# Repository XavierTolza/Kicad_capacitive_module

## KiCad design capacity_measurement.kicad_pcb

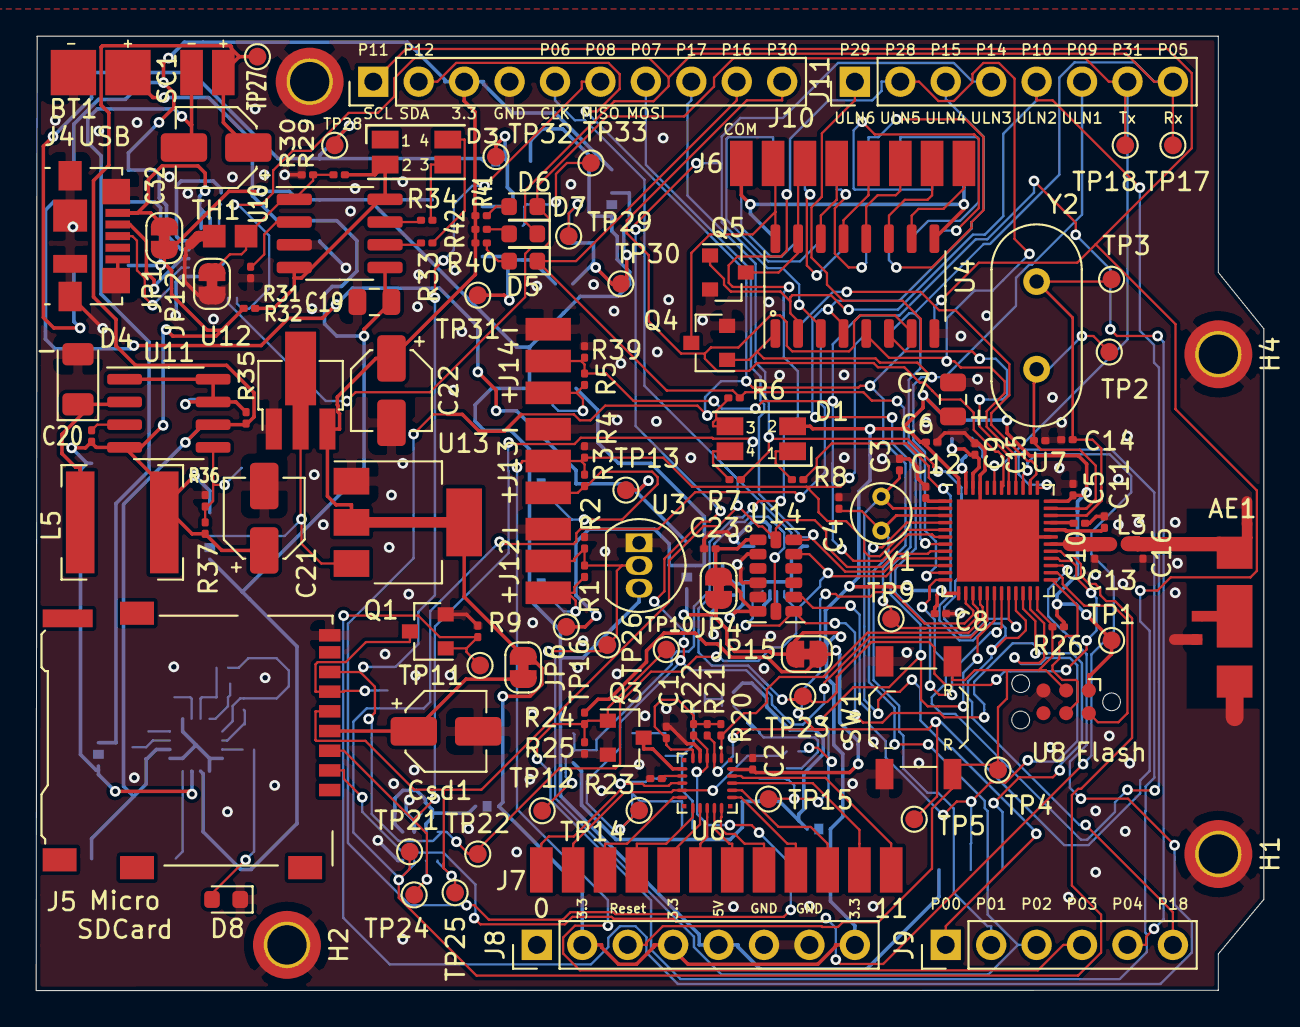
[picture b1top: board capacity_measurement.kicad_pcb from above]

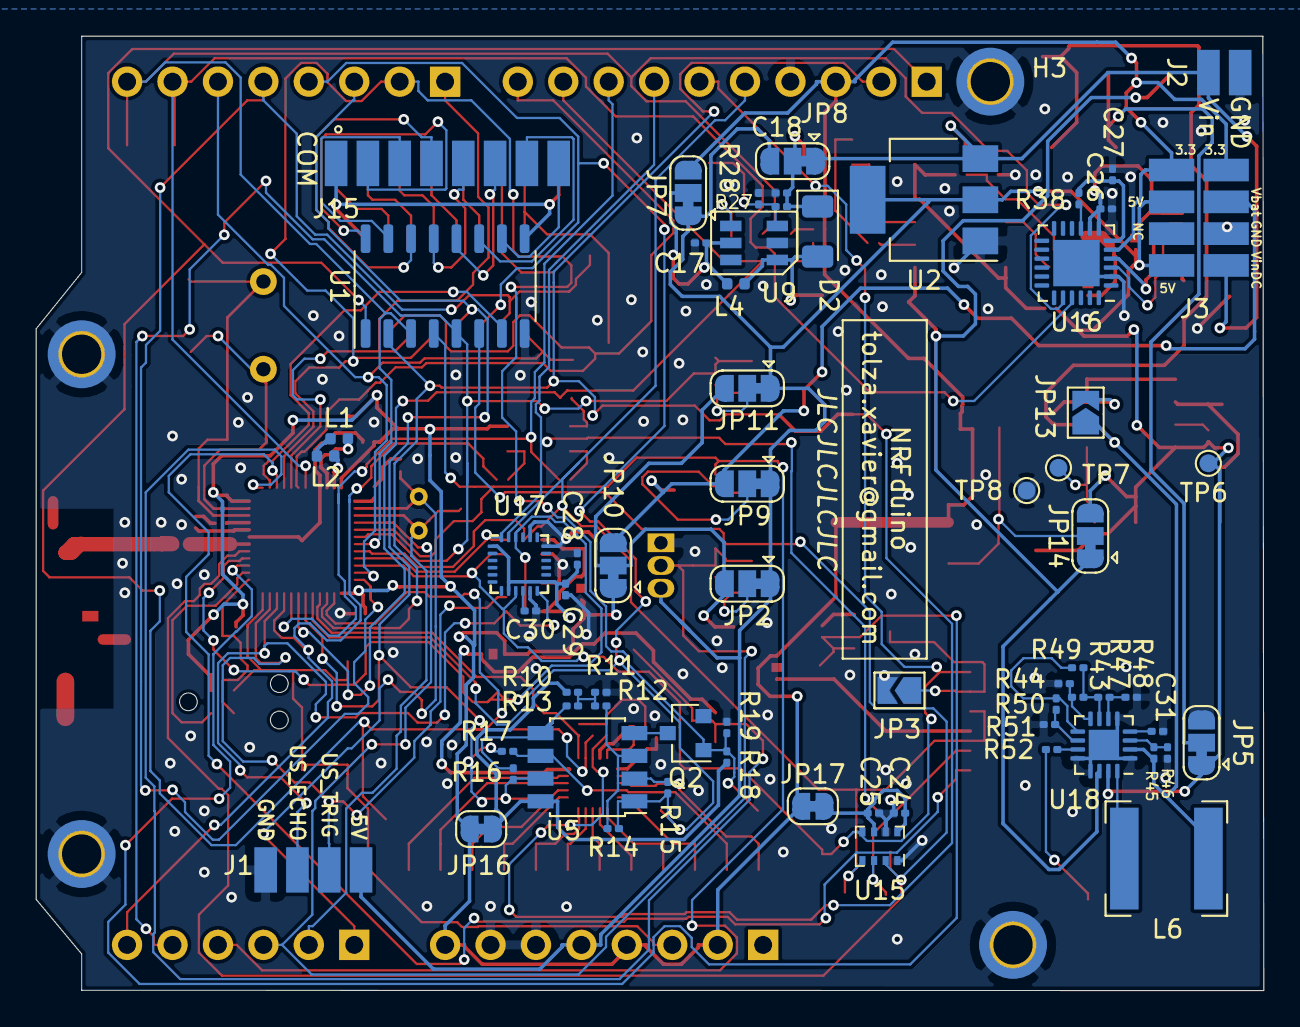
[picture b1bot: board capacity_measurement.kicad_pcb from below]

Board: 2 copper layers, 68.6 x 53.4 mm, 196 parts (66 on the bottom side), 135 nets.

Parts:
AE1: Antenna_Dipole; taoglass_LA02_antenna
BT1: Bat; smdpad_01x02_2.54_2.54_0.51
C1, C2, C29, C30: 0.1uF; C_0201_0603Metric
C3, C4, C26, C27, C31: C; C_0201_0603Metric
C5, C6, C8, C12: 100nF; C_0201_0603Metric
C7: 4.7uF; C_0805_2012Metric
C9, C23, C24, C25: 1uF; C_0201_0603Metric
C10: 100pF; C_0201_0603Metric
C11, C16: NC; C_0201_0603Metric
C13: 0.8pF; C_0201_0603Metric
C14, C15: 12pF; C_0201_0603Metric
C17, C18: 22uF; C_0201_0603Metric
C19: 10uF; C_0805_2012Metric
C20: 280pF; C_0201_0603Metric
C21: >=23uF; CP_Elec_4x3
C22: 10uF; CP_Elec_4x3
C28: 10nF; C_0201_0603Metric
C32: CP; CP_Elec_4x3
Csd1: CP; CP_Elec_4x3
D1, D3: LED_BARG; LED_RGB_1210
D2, D4: D_Schottky; D_1206_3216Metric
D5, D6, D7, D8: LED; LED_0603_1608Metric
H1, H2, H3, H4: Fix; MountingHole_2.2mm_M2_DIN965_Pad_TopBottom
J1: Ultrasound; smdpad_01x04_1.27_2.54_0.51
J2: Conn_01x02; smdpad_01x02_1.27_2.54_0.51
J3: PWR_CONN; smdpad_02x04_1.27_2.54_0.51
J4: USB_B_Micro; USB_Micro-B_Molex_47346-0001
J5: Micro_SD_Card; microSD
J6, J15: Conn_01x08; smdpad_01x08_1.27_2.54_0.51
J7: Conn_01x12; smdpad_01x12_1.27_2.54_0.51
J8, J11: Conn_01x08; PinHeader_1x08_P2.54mm_Vertical
J9: Conn_01x06; PinHeader_1x06_P2.54mm_Vertical
J10: Conn_01x10; PinHeader_1x10_P2.54mm_Vertical
J12, J13, J14: Conn_01x03; smdpad_01x03_1.27_2.54_0.51
JP1: USB_5V; SolderJumper-2_P1.3mm_Bridged_RoundedPad1.0x1.5mm
JP2: Bridge1; SolderJumper-3_P1.3mm_Bridged12_RoundedPad1.0x1.5mm
JP3: SD_EN; SolderJumper-2_P1.3mm_Open_TrianglePad1.0x1.5mm
JP4: Vacc; SolderJumper-2_P1.3mm_Bridged_RoundedPad1.0x1.5mm
JP5, JP14: Vbat; SolderJumper-3_P1.3mm_Bridged12_RoundedPad1.0x1.5mm
JP6, JP17: Vsd; SolderJumper-2_P1.3mm_Bridged_RoundedPad1.0x1.5mm
JP7: Boost_in; SolderJumper-3_P1.3mm_Bridged12_RoundedPad1.0x1.5mm
JP8: Boost_out; SolderJumper-3_P1.3mm_Bridged12_RoundedPad1.0x1.5mm
JP9: Bridge2; SolderJumper-3_P1.3mm_Bridged12_RoundedPad1.0x1.5mm
JP10: Temp_NTC; SolderJumper-3_P1.3mm_Bridged12_RoundedPad1.0x1.5mm
JP11: Bridge3; SolderJumper-3_P1.3mm_Bridged12_RoundedPad1.0x1.5mm
JP12: TempEN; SolderJumper-2_P1.3mm_Bridged_RoundedPad1.0x1.5mm
JP13: shunt; SolderJumper-2_P1.3mm_Open_TrianglePad1.0x1.5mm
JP15: Vmpr; SolderJumper-2_P1.3mm_Bridged_RoundedPad1.0x1.5mm
JP16: Vaop; SolderJumper-2_P1.3mm_Bridged_RoundedPad1.0x1.5mm
L1, L4: 10uH; L_0402_1005Metric
L2: 15nH; L_0402_1005Metric
L3: 3.9nH; L_0402_1005Metric
L5, L6: >=26uH; L_Bourns-SRN6028
Q1, Q2, Q3, Q4, Q5: 2N7002; SOT-23
R1, R2, R3, R4, R5, R6, R7, R8, R9, R10, R11, R12, R13, R14, R15, R16, R17, R18, R19, R20, R21, R22, R24, R25, R29, R30, R38, R39, R40, R41, R42, R43, R44, R45, R46, R47, R48, R49, R50, R51, R52: R; R_0201_0603Metric
R23: 75K 1%; R_0201_0603Metric
R26, R31: 10k; R_0201_0603Metric
R27: 37k; R_0201_0603Metric
R28: 5k; R_0201_0603Metric
R32: 0.4; R_0201_0603Metric
R33, R34, R36: 1k; R_0201_0603Metric
R35: 0.45; R_0201_0603Metric
R37: 3.4k; R_0201_0603Metric
SC1: Solar_Cell; smdpad_01x02_1.27_2.54_0.51
SW1: SW_Push; SW_SPST_TL3342
TH1: NTC; smdpad_01x02_1.27_1.27_0.51
TP1: Vmcu; TestPoint_Pad_D1.0mm
TP2: XC2; TestPoint_Pad_D1.0mm
TP3: XC1; TestPoint_Pad_D1.0mm
TP4: Reset; TestPoint_Pad_D1.0mm
TP5: SCL; TestPoint_Pad_D1.0mm
TP6: GNDD; TestPoint_Pad_D1.0mm
TP7: BB_FB; TestPoint_Pad_D1.0mm
TP8: GND; TestPoint_Pad_D1.0mm
TP9: SDA; TestPoint_Pad_D1.0mm
TP10: MPR_EN; TestPoint_Pad_D1.0mm
TP11: SD_EN; TestPoint_Pad_D1.0mm
TP12: AOP_EN; TestPoint_Pad_D1.0mm
TP13: Vbat; TestPoint_Pad_D1.0mm
TP14: AOP1; TestPoint_Pad_D1.0mm
TP15: AOP2; TestPoint_Pad_D1.0mm
TP16: Vbridge; TestPoint_Pad_D1.0mm
TP17: Rx; TestPoint_Pad_D1.0mm
TP18: Tx; TestPoint_Pad_D1.0mm
TP21: PRESSURE_CS; TestPoint_Pad_D1.0mm
TP22: MISO; TestPoint_Pad_D1.0mm
TP23: ACC_nCS; TestPoint_Pad_D1.0mm
TP24, TP25: MOSI; TestPoint_Pad_D1.0mm
TP26: TEMP_DQ; TestPoint_Pad_D1.0mm
TP27: Vsolar; TestPoint_Pad_D1.0mm
TP28: VinDC; TestPoint_Pad_D1.0mm
TP29: BoostEN; TestPoint_Pad_D1.0mm
TP30: BoostVin; TestPoint_Pad_D1.0mm
TP31: SW; TestPoint_Pad_D1.0mm
TP32: Vout; TestPoint_Pad_D1.0mm
TP33: BoostFB; TestPoint_Pad_D1.0mm
U1, U4: ULN2003; STC_SOP-16_3.9x9.9mm_P1.27mm
U2: AMS1117-5.0; SOT-223-3_TabPin2
U3: DS18B20; TO-92_Inline
U5: Opamp_Dual_Generic; SSOP-8_3.95x5.21x3.27mm_P1.27mm
U6: MPR121; Texas_S-PWQFN-N20
U7: nRF52832-QFxx; QFN-48-1EP_6x6mm_P0.4mm_EP4.6x4.6mm
U8: TagConnect; Tag-Connect_TC2030-IDC-NL_2x03_P1.27mm_Vertical
U9: SX1308
U10: TP4056; SOP-8_3.76x4.96mm_P1.27mm
U11: MC34063AD; SOIC-8_3.9x4.9mm_P1.27mm
U12: HT7127-1-SOT89; SOT-89-3_Handsoldering
U13: AMS1117-2.85; SOT-223-3_TabPin2
U14: ADXL343; LGA-14_3x5mm_P0.8mm_LayoutBorder1x6y
U15: BMP280; Bosch_LGA-8_2x2.5mm_P0.65mm_ClockwisePinNumbering
U16: CP2102N-A01-GQFN24; QFN-24-1EP_4x4mm_P0.5mm_EP2.6x2.6mm
U17: MPU-9250; InvenSense_QFN-24_3x3mm_P0.4mm
U18: BQ25504; QFN-16-1EP_3x3mm_P0.5mm_EP1.7x1.7mm
Y1: 32.768k; Crystal_C38-LF_D3.0mm_L8.0mm_Vertical
Y2: 32MHz; Crystal_HC18-U_Vertical

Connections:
+3V3: C5.1, C6.1, C7.1, C8.1, C22.1, D1.2, J3.1, J3.2, J8.2, J8.4, J8.8, J10.3, JP4.1, JP6.1, JP7.3, JP10.1, JP15.1, JP16.1, JP17.1, R26.1, R40.1, R41.1, R42.1, TP1.1, U7.13, U7.36, U7.48, U8.1, U12.3, U13.2, U16.5
+5V: C20.2, C21.1, J1.4, J3.4, J3.8, J8.5, JP1.1, JP2.1, JP5.1, JP7.1, JP8.3, JP9.1, JP11.1, JP14.3, L5.2, R32.1, R37.1, TP6.1, U2.2, U3.3, U11.4, U18.15
/ACC_INT1: J1.2, U7.22, U14.8, U17.12
/ACC_INT2: J1.3, U7.23, U14.9
/ACC_nCS: TP23.1, U7.28, U14.7, U17.22
/AOP1: J11.4, R14.1, R15.1, TP14.1, U4.3, U5.1, U7.17
/AOP2: J11.3, R16.1, R17.1, TP15.1, U4.4, U5.7, U7.18
/AOP_EN: J11.2, Q2.1, R18.2, R19.1, TP12.1, U4.5, U7.40
/BOOST_EN: U1.7, U7.38
/CLK: J5.5, J10.5, TP25.1, U7.8, U14.14, U15.4, U17.23
/MISO: J5.7, J10.6, TP22.1, U7.10, U14.12, U15.5, U17.9
/MOSI: J5.3, J10.7, TP24.1, U7.9, U14.13, U15.3, U17.24
/MPR_EN: Q3.1, R24.2, R25.1, TP10.1, U7.37
/MPR_nIRQ: R20.1, U6.1, U7.16
/P00: C3.1, J9.1, U7.2, Y1.1
/P01: C4.1, J9.2, U7.3, Y1.2
/P02: J9.3, J12.2, R1.2, R2.1, TP26.1, U3.2, U7.4
/P03: J9.4, J13.2, R3.2, R4.1, U1.4, U7.5
/P04: J9.5, J14.2, R5.2, R39.1, U1.5, U7.6
/P16: D5.1, J10.9, R6.1, U7.19
/P17: J10.8, R7.1, U7.20
/P18: J9.6, R8.1, U7.21
/P29: J11.1, U4.6, U7.41
/P30: J10.10, U4.7, U7.42
/PRESSURE_CS: TP21.1, U1.6, U7.29, U15.2
/RESET: J8.3, R26.2, SW1.2, TP4.1, U7.24, U8.3
/Rx: D7.1, J11.8, TP17.1, U1.3, U7.7, U16.20
/SCL: J10.1, R21.1, TP5.1, U1.1, U6.2, U7.14
/SDA: J10.2, R22.1, TP9.1, U1.2, U6.3, U7.15
/SD_CS: J5.2, U7.39
/SD_EN: Q1.1, R9.1, TP11.1, U7.27
/Tx: D6.1, J11.7, TP18.1, U7.43, U16.21
/ULN1: J11.6, Q4.1, U4.1, U7.11
/ULN2: J11.5, Q5.1, U4.2, U7.12
/Vacc: C23.1, C28.1, C29.2, JP4.2, U14.1, U14.6, U17.1, U17.8, U17.13
/Vbat: J3.3, JP9.3, JP10.3, TP13.1
/Vbridge: JP2.3, JP10.2, JP11.3, TP16.1
/VinDC: J2.1, J3.7, JP8.1, TP28.1, U2.3
/capacitive_sensor/MPR0: J7.1, R15.2, U5.2, U6.8
/capacitive_sensor/MPR1: J7.2, R17.2, U5.6, U6.9
/capacitive_sensor/MPR2: J7.3, U6.10
/capacitive_sensor/MPR3: J7.4, U6.11
/capacitive_sensor/MPR4: J7.5, U6.12
/capacitive_sensor/MPR5: J7.6, U6.13
/capacitive_sensor/MPR6: J7.7, U6.14
/capacitive_sensor/MPR7: J7.8, U6.15
/capacitive_sensor/MPR8: J7.9, U6.16
/capacitive_sensor/MPR9: J7.10, U6.17
/capacitive_sensor/MPR10: J7.11, U6.18
/capacitive_sensor/MPR11: J7.12, U6.19
/capacitive_sensor/MPR_Vss: Q3.3, U6.6
/capacitive_sensor/Vaop: JP16.2, R10.2, R18.1, U5.8
/capacitive_sensor/Vmpr: C2.1, JP15.2, R24.1, U6.20
/ftdi/DM: J4.2, U16.4
/ftdi/DP: J4.3, U16.3
/ftdi/Vdd: C27.1, R38.1, U16.6
/ftdi/Vusb: C26.1, J4.1, JP1.2, U16.7, U16.8
/interfaces/Vsd: Csd1.1, J5.4, JP6.2
/low_end_driver/DRV1: J6.2, Q4.3, U4.16
/low_end_driver/DRV2: J6.3, Q5.3, U4.15
/low_end_driver/DRV3: J6.4, U4.14
/low_end_driver/DRV4: J6.5, U4.13
/low_end_driver/DRV5: J6.6, U4.12
/low_end_driver/DRV6: J6.7, U4.11
/low_end_driver/DRV7: J6.8, U4.10
/low_end_driver/DRV8: J15.2, U1.16
/low_end_driver/DRV9: J15.3, U1.15
/low_end_driver/DRV10: J15.4, U1.14
/low_end_driver/DRV11: J15.5, U1.13
/low_end_driver/DRV12: J15.6, U1.12
/low_end_driver/DRV13: J15.7, U1.11
/low_end_driver/DRV14: J15.8, U1.10
/low_end_driver/ULN_COM: J6.1, J15.1, U1.9, U4.9
/mcu/ANT: AE1.1, C16.1, L3.1
/mcu/DCC: L2.1, U7.47
/mcu/DEC1: C12.2, U7.1
/mcu/DEC2: C11.2, U7.32
/mcu/DEC3: C10.2, U7.33
/mcu/DEC4: C9.2, L1.2, U7.46
/mcu/RF_out: C13.1, L3.2, U7.30
/mcu/SWDCLK: U7.25, U8.4
/mcu/SWDIO: U7.26, U8.2
/power_management/BOOST_EN: TP29.1, U9.4
/power_management/Vbat: BT1.1, C19.1, JP14.1, U10.5, U18.14
/power_management/sheet618CA8D8/Boost_FB: R27.2, R28.1, TP33.1, U9.3
/power_management/sheet618CA8D8/Boost_SW: D2.2, L4.2, TP31.1, U9.1
/power_management/sheet618CA8D8/Vin: C17.1, JP7.2, L4.1, TP30.1, U9.5
/power_management/sheet618CA8D8/Vout: C18.1, D2.1, JP8.2, R27.1, TP32.1
/power_management/sheet618CA8D9/TP4056_Vcc: D3.2, R29.1, R32.2, U10.4, U10.8
/power_management/sheet618CA8DA/BB_DC: JP13.2, R35.1, U11.1, U11.7, U11.8
/power_management/sheet618CA8DA/BB_FB: R36.1, R37.2, TP7.1, U11.5
/power_management/sheet618CA8DA/BB_SWE: D4.1, L5.1, U11.2
/power_management/sheet618CA8DA/BB_TC: C20.1, U11.3
/power_management/sheet618CA8DA/OK_HIST: R49.1, R50.2, U18.9
/power_management/sheet618CA8DA/OK_PROG: R50.1, R51.2, U18.10
/power_management/sheet618CA8DA/SOLAR+: C32.1, JP13.1, L6.1, R35.2, R45.2, SC1.1, TP27.1, U11.6, U18.2
/power_management/sheet618CA8DA/SOLAR-: C32.2, JP5.2, SC1.2
/power_management/sheet618CA8DA/VOC_SAMP: R45.1, R46.2, U18.3
/power_management/sheet618CA8DA/VR_DIV: R43.2, R47.2, R49.2, U18.7
/power_management/sheet618CA8DA/Vbat_OV: R47.1, R48.2, U18.6
/power_management/sheet618CA8DA/Vbat_UV: R43.1, R44.2, U18.8
/pressure_sensor/Vin: C24.1, C25.2, JP17.2, U15.6, U15.8
GND: AE1.2, BT1.2, C1.2, C2.2, C3.2, C4.2, C5.2, C6.2, C7.2, C8.2, C9.1, C10.1, C11.1, C12.1, C13.2, C14.2, C15.2, C16.2, C17.2, C18.2, C19.2, C21.2, C22.2, C23.2, C24.2, C25.1, C26.2, C27.2, C28.2, C29.1, C30.1, C31.2, Csd1.2, D4.2, D8.1, H1.1, H2.1, H3.1, H4.1, J1.1, J2.2, J3.5, J4.5, J4.6, J5.9, J8.6, J8.7, J10.4, J12.3, J13.3, J14.3, JP3.2, JP5.3, JP12.1, Q1.2, Q2.2, Q3.2, Q4.2, Q5.2, R2.2, R4.2, R9.2, R11.1, R19.2, R23.2, R25.2, R28.2, R30.2, R31.2, R36.2, R39.2, R44.1, R46.1, R48.1, R51.1, SW1.1, TH1.1, TP8.1, U1.8, U2.1, U3.1, U4.8, U6.4, U7.31, U7.45, U7.49, U8.5, U9.2, U10.3, U12.1, U13.1, U14.2, U14.4, U14.5, U15.1, U15.7, U16.2, U16.25, U17.11, U17.18, U17.20, U18.1, U18.5, U18.12, U18.13, U18.17
unnamed: C1.1, R20.2, R21.2, R22.2, U6.5
unnamed: C14.1, TP3.1, U7.34, Y2.1
unnamed: C15.1, TP2.1, U7.35, Y2.2
unnamed: C30.2, U17.10
unnamed: C31.1, U18.4
unnamed: D1.1, R8.2
unnamed: D1.3, R6.2
unnamed: D1.4, R7.2
unnamed: D3.3, R34.2
unnamed: D3.4, R33.2
unnamed: D5.2, R40.2
unnamed: D6.2, R41.2
unnamed: D7.2, R42.2
unnamed: D8.2, R52.2
unnamed: J5.6, JP3.1, Q1.3
unnamed: J12.1, JP2.2, R1.1
unnamed: J13.1, JP9.2, R3.1
unnamed: J14.1, JP11.2, R5.1
unnamed: JP12.2, R29.2, R30.1, TH1.2, U10.1
unnamed: JP14.2, U12.2, U13.3
unnamed: L1.1, L2.2
unnamed: L6.2, U18.16
unnamed: Q2.3, U5.4
unnamed: R10.1, R11.2, R12.2, R13.2
unnamed: R12.1, R14.2, U5.3
unnamed: R13.1, R16.2, U5.5
unnamed: R23.1, U6.7
unnamed: R31.1, U10.2
unnamed: R33.1, U10.6
unnamed: R34.1, U10.7
unnamed: R38.2, U16.9
unnamed: R52.1, U18.11

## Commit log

2021-10-29 séparation en plusieurs feuilles
2021-10-29 redécoupage encore plus poussé
2021-10-29 wip arduino pinout
2021-10-29 assigned footprints
2021-11-10 changed resistor size
2021-11-10 finished placing
2021-11-10 antenna connexion
2021-11-12 wip routage
2021-11-14 finished routing
2021-11-16 WIP silkscreen
2021-11-18 finished silkscreen
